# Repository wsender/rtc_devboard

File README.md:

# rtc_devboard

This is a small development board for an upcoming nixie tub project I'm doing.

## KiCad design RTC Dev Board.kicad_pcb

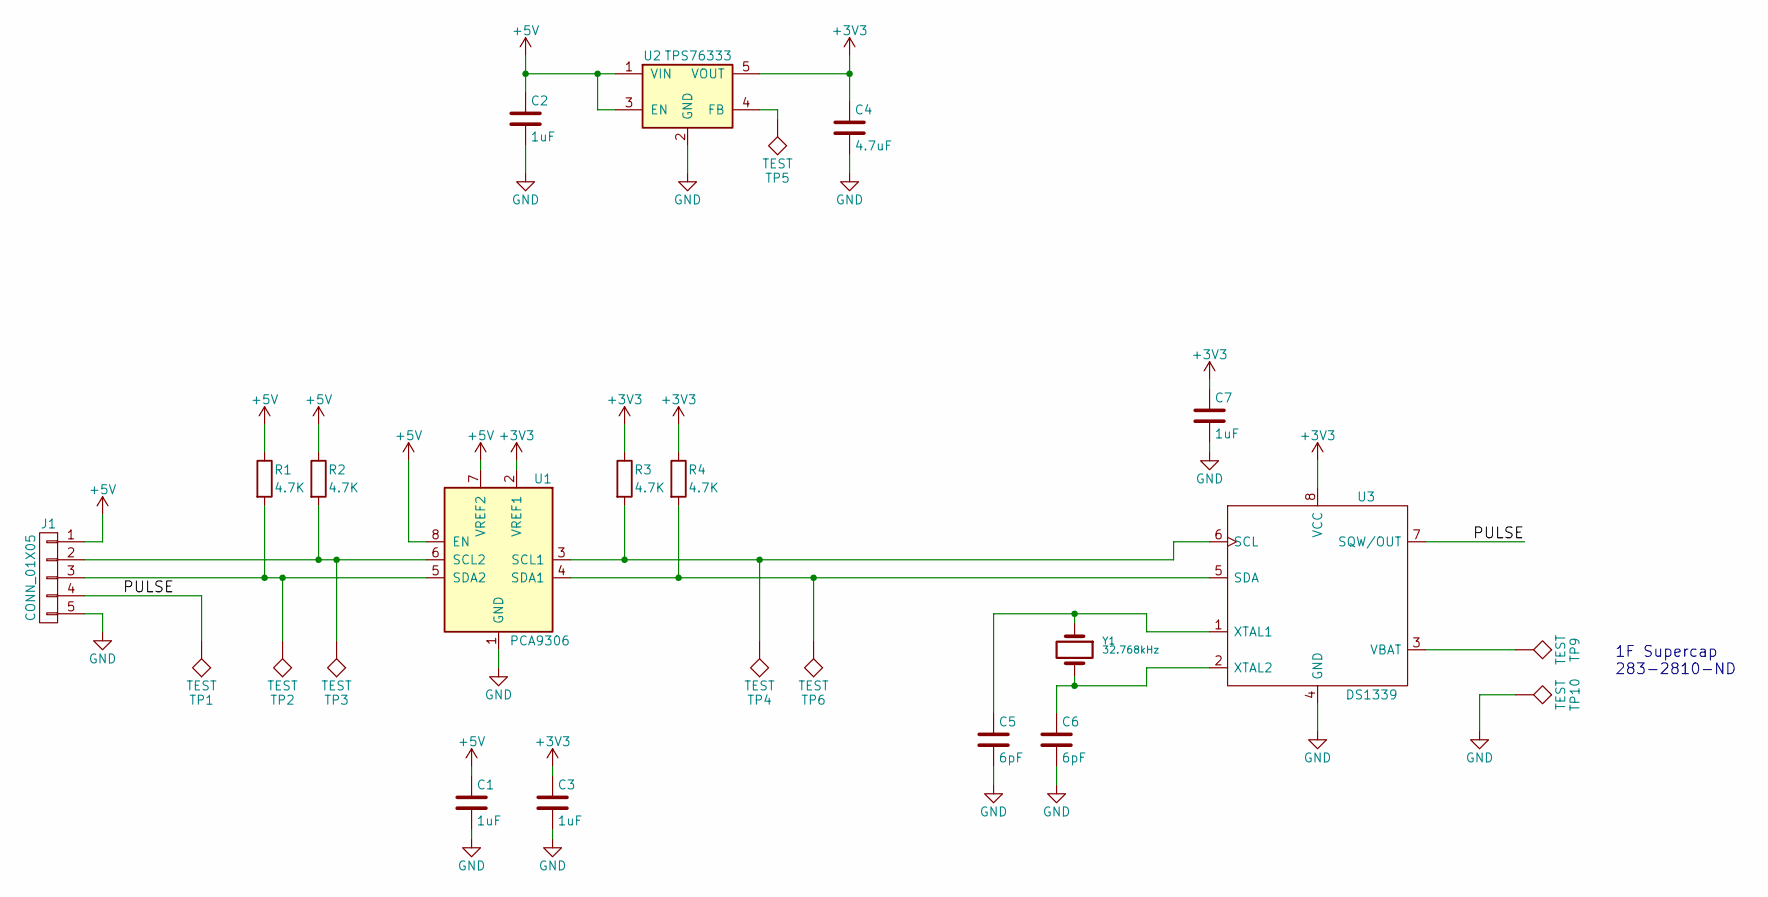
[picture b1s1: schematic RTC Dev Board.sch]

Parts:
C1, C2, C3, C7: 1uF; C_0603_HandSoldering
C4: 4.7uF; C_0603_HandSoldering
C5, C6: 6pF; C_0603_HandSoldering
J1: CONN_01X05; Socket_Strip_Straight_1x05_Pitch2.54mm
R1, R2, R3, R4: 4.7K; R_0603_HandSoldering
TP1, TP2, TP3, TP4, TP5, TP6, TP9, TP10: TEST; Measurement_Point_Round-TH_Small
U1: PCA9306; SSOP-8_2.95x2.8mm_Pitch0.65mm
U2: TPS76333; SOT-23-5
U3: DS1339; SSOP-8_2.95x2.8mm_Pitch0.65mm
Y1: 32.768kHz; R_1206_HandSoldering; DigiKeyPN 535-12942-1-ND

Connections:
+3V3: C3.1, C4.1, C7.1, R3.1, R4.1, U1.2 (VREF1), U2.5 (VOUT), U3.8 (VCC)
+5V: C1.1, C2.1, J1.1, R1.1, R2.1, U1.7 (VREF2), U1.8 (EN), U2.1 (VIN), U2.3 (EN)
/PULSE: J1.4, TP1.1, U3.7 (SQW/OUT)
GND: C1.2, C2.2, C3.2, C4.2, C5.2, C6.2, C7.2, J1.5, TP10.1, U1.1 (GND), U2.2 (GND), U3.4 (GND)
unnamed: C5.1, U3.1 (XTAL1), Y1.1
unnamed: C6.1, U3.2 (XTAL2), Y1.2
unnamed: J1.2, R2.2, TP3.1, U1.6 (SCL2)
unnamed: J1.3, R1.2, TP2.1, U1.5 (SDA2)
unnamed: R3.2, TP4.1, U1.3 (SCL1), U3.6 (SCL)
unnamed: R4.2, TP6.1, U1.4 (SDA1), U3.5 (SDA)
unnamed: TP5.1, U2.4 (FB)
unnamed: TP9.1, U3.3 (VBAT)

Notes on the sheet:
1F Supercap 283-2810-ND

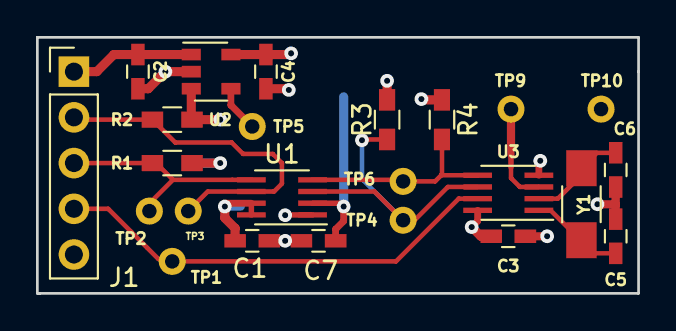
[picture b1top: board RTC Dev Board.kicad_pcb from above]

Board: 2 copper layers, 33.4 x 14.2 mm, 24 parts (0 on the bottom side), 12 nets.

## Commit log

2017-04-02 initial commit
    KiCAD schematic and layout for RTC dev board.
2017-04-11 Set theme jekyll-theme-midnight
